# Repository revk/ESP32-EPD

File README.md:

# ESP32-EPD

Now at [Codeberg](https://codeberg.org/RevK/ESP32-EPD)

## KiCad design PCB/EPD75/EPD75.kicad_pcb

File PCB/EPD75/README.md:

# EPD75

These files are for use in [KiCad](https://www.kicad.org).

## Trademark

This is an open source project, but bear in mind you cannot sell boards bearing the Andrews & Arnold Ltd name, the A&A logo, the registered trademark AJK logo, or the GS1 allocated EANs assigned to Andrews & Arnold Ltd.

## Images

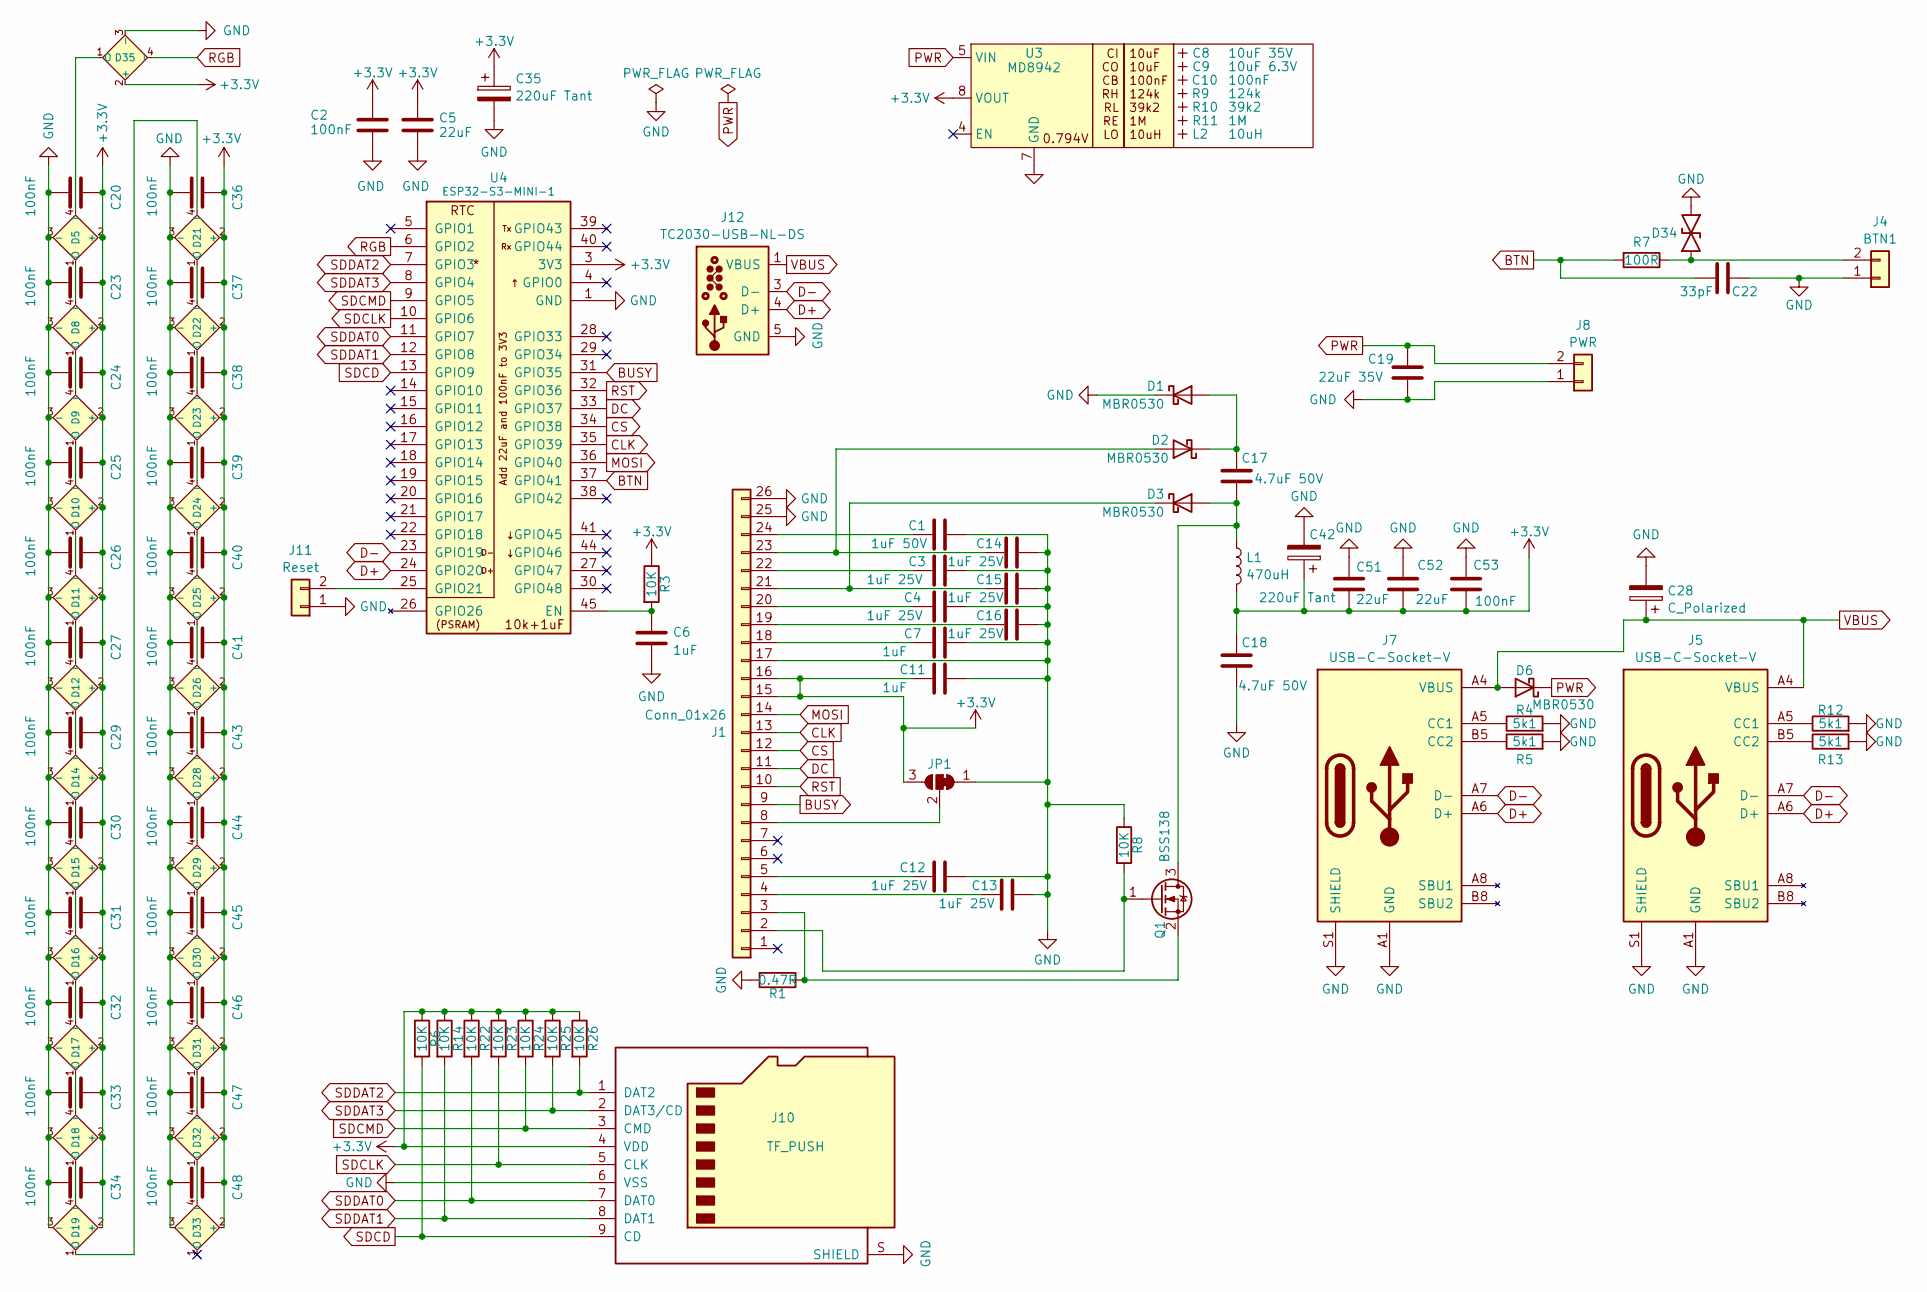
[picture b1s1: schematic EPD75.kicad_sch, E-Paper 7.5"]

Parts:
C1: 1uF 50V; C_0603
C2, C20, C23, C24, C25, C26, C27, C29, C30, C31, C32, C33, C34, C36, C37, C38, C39, C40, C41, C43, C44, C45, C46, C47, C48, C53: 100nF; C_0402
C3, C4, C12, C13, C14, C15, C16: 1uF 25V; C_0402
C5, C51, C52: 22uF; C_0603
C6, C7, C11: 1uF; C_0402
C8: 10uF 35V; C_0603_; MPN C194427
C9: 10uF 6.3V; C_0603_; MPN C1691
C10: 100nF; C_0603_
C17, C18: 4.7uF 50V; C_0805
C19: 22uF 35V; C_1210
C22: 33pF; C_0402
C28: C_Polarized; CP_EIA-7343-31_Kemet-D; MPN C106188
C35, C42: 220uF Tant; CP_EIA-3528-21_Kemet-B; MPN C122649
D1, D2, D3, D6: MBR0530; D_SOD-123; MPN C5204746
D5, D8, D9, D10, D11, D12, D14, D15, D16, D17, D18, D19, D21, D22, D23, D24, D25, D26, D28, D29, D30, D31, D32, D33, D35: XL-1010RGBC-WS2812B; MPN C5349953
D34: DFN1006-2L; MPN C5137770
J1: Conn_01x26; XUNPU-FPC-05FB-24PH20; MPN C2856831
J4: BTN1; WAGO-2060-452-998-404; MPN C2765055
J5, J7: USB-C-Socket-V; USB-C-Socket-H; MPN C709357
J8: PWR; WAGO-2060-452-998-404; MPN C2765055
J10: TF_PUSH; MPN C393941
J11: Reset; AA-Pad
J12: TC2030-USB-NL-DS; Tag-Connect_TC2030-IDC-NL_2x03_P1.27mm_Vertical
JP1: SolderJumper_3_Bridged12; SolderJumper3
L1: 470uH; L_4x4; MPN C42429207
L2: 10uH; L_4x4_; MPN C167879
Q1: BSS138; SOT-23; MPN C2938375
R1: 0.47R; R_0402; MPN C2771738
R3, R6, R8, R14, R22, R23, R24, R25, R26: 10K; R_0402
R4, R5, R12, R13: 5k1; R_0402
R7: 100R; R_0402
R9: 124k; R_0402_; MPN C138062
R10: 39k2; R_0402_
R11: 1M; R_0402_
U3: MD8942; SOT-23-6-MD8942; MPN C2684786
U4: ESP32-S3-MINI-1; MPN C3013941

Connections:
+3.3V: C2.1, C5.1, C11.1, C18.2, C20.1, C23.1, C24.1, C25.1, C26.1, C27.1, C29.1, C30.1, C31.1, C32.1, C33.1, C34.1, C35.1, C36.1, C37.1, C38.1, C39.1, C40.1, C41.1, C42.1, C43.1, C44.1, C45.1, C46.1, C47.1, C48.1, C51.2, C52.2, C53.2, D5.2 (+), D8.2 (+), D9.2 (+), D10.2 (+), D11.2 (+), D12.2 (+), D14.2 (+), D15.2 (+), D16.2 (+), D17.2 (+), D18.2 (+), D19.2 (+), D21.2 (+), D22.2 (+), D23.2 (+), D24.2 (+), D25.2 (+), D26.2 (+), D28.2 (+), D29.2 (+), D30.2 (+), D31.2 (+), D32.2 (+), D33.2 (+), D35.2 (+), J1.15, J1.16, J10.4 (VDD), JP1.3 (B), L1.2, R3.1, R6.1, R14.1, R22.1, R23.1, R24.1, R25.1, R26.1, U3.8 (VOUT), U4.3 (3V3)
BTN: C22.1, R7.2, U4.37 (GPIO41)
BUSY: J1.9, U4.31 (GPIO35)
CLK: J1.13, U4.35 (GPIO39)
CS: J1.12, U4.34 (GPIO38)
D+: J5.A6 (D+), J5.B6 (D+), J7.A6 (D+), J7.B6 (D+), J12.4 (D+), U4.24 (GPIO20)
D-: J5.A7 (D-), J5.B7 (D-), J7.A7 (D-), J7.B7 (D-), J12.2 (NC), J12.3 (D-), J12.6 (NC), U4.23 (GPIO19)
DC: J1.11, U4.33 (GPIO37)
GND: C1.2, C2.2, C3.2, C4.2, C5.2, C6.2, C7.2, C11.2, C12.2, C14.2, C15.2, C18.1, C19.2, C20.2, C22.2, C23.2, C24.2, C25.2, C26.2, C27.2, C28.2, C29.2, C30.2, C31.2, C32.2, C33.2, C34.2, C35.2, C36.2, C37.2, C38.2, C39.2, C40.2, C41.2, C42.2, C43.2, C44.2, C45.2, C46.2, C47.2, C48.2, C51.1, C52.1, C53.1, D1.1 (K), D5.3 (-), D8.3 (-), D9.3 (-), D10.3 (-), D11.3 (-), D12.3 (-), D14.3 (-), D15.3 (-), D16.3 (-), D17.3 (-), D18.3 (-), D19.3 (-), D21.3 (-), D22.3 (-), D23.3 (-), D24.3 (-), D25.3 (-), D26.3 (-), D28.3 (-), D29.3 (-), D30.3 (-), D31.3 (-), D32.3 (-), D33.3 (-), D34.1, D35.3 (-), J1.17, J1.25, J1.26, J4.1, J5.A1 (GND), J5.A12 (GND), J5.B1 (GND), J5.B12 (GND), J5.S1 (SHIELD), J7.A1 (GND), J7.A12 (GND), J7.B1 (GND), J7.B12 (GND), J7.S1 (SHIELD), J8.1, J10.6 (VSS), J10.S (SHIELD), J11.1, J12.5 (GND), JP1.1 (A), R1.2, R4.2, R5.2, R8.1, R12.2, R13.2, U3.2 (GND), U3.7 (GND), U4.1 (GND), U4.2 (GND), U4.42 (GND), U4.43 (GND), U4.46 (GND), U4.47 (GND), U4.48 (GND), U4.49 (GND), U4.50 (GND), U4.51 (GND), U4.52 (GND), U4.53 (GND), U4.54 (GND), U4.55 (GND), U4.56 (GND), U4.57 (GND), U4.58 (GND), U4.59 (GND), U4.60 (GND), U4.61 (GND), U4.62 (GND), U4.63 (GND), U4.64 (GND), U4.65 (GND)
MOSI: J1.14, U4.36 (GPIO40)
unnamed: C17.2, D1.2 (A), D2.1 (K)
unnamed: C14.1, D2.2 (A), J1.23
unnamed: C17.1, D3.2 (A), L1.1, Q1.3 (D)
unnamed: C15.1, D3.1 (K), J1.21
unnamed: D5.1 (O), D8.4 (I)
unnamed: D8.1 (O), D9.4 (I)
unnamed: D9.1 (O), D10.4 (I)
unnamed: D10.1 (O), D11.4 (I)
unnamed: D11.1 (O), D12.4 (I)
unnamed: D12.1 (O), D14.4 (I)
unnamed: D14.1 (O), D15.4 (I)
unnamed: D15.1 (O), D16.4 (I)
unnamed: D16.1 (O), D17.4 (I)
unnamed: D17.1 (O), D18.4 (I)
unnamed: D18.1 (O), D19.4 (I)
unnamed: D19.1 (O), D21.4 (I)
unnamed: D21.1 (O), D22.4 (I)
unnamed: D22.1 (O), D23.4 (I)
unnamed: D23.1 (O), D24.4 (I)
unnamed: D24.1 (O), D25.4 (I)
unnamed: D25.1 (O), D26.4 (I)
unnamed: D26.1 (O), D28.4 (I)
unnamed: D28.1 (O), D29.4 (I)
unnamed: D29.1 (O), D30.4 (I)
unnamed: D30.1 (O), D31.4 (I)
unnamed: D31.1 (O), D32.4 (I)
unnamed: D32.1 (O), D33.4 (I)
unnamed: D5.4 (I), D35.1 (O)
unnamed: J1.2, Q1.1 (G), R8.2
unnamed: J1.3, Q1.2 (S), R1.1
unnamed: C12.1, J1.5
unnamed: J1.8, JP1.2 (C)
unnamed: C7.1, J1.18
unnamed: C4.1, J1.20
unnamed: C1.1, J1.24
unnamed: D34.2, J4.2, R7.1
unnamed: J5.A5 (CC1), R12.1
unnamed: J5.B5 (CC2), R13.1
unnamed: J7.A5 (CC1), R4.1
unnamed: J7.B5 (CC2), R5.1
unnamed: J11.2, U4.25 (GPIO21)
unnamed: C6.1, R3.2, U4.45 (EN)
PWR: C19.1, D6.1 (K), J8.2, U3.5 (VIN)
RGB: D35.4 (I), U4.6 (GPIO2)
RST: J1.10, U4.32 (GPIO36)
SDCD: J10.9 (CD), R6.2, U4.13 (GPIO9)
SDCLK: J10.5 (CLK), R23.2, U4.10 (GPIO6)
SDCMD: J10.3 (CMD), R24.2, U4.9 (GPIO5)
SDDAT0: J10.7 (DAT0), R22.2, U4.11 (GPIO7)
SDDAT1: J10.8 (DAT1), R14.2, U4.12 (GPIO8)
SDDAT2: J10.1 (DAT2), R26.2, U4.7 (GPIO3)
SDDAT3: J10.2 (DAT3/CD), R25.2, U4.8 (GPIO4)
VBUS: C28.1, D6.2 (A), J5.A4 (VBUS), J5.A9 (VBUS), J5.B4 (VBUS), J5.B9 (VBUS), J7.A4 (VBUS), J7.A9 (VBUS), J7.B4 (VBUS), J7.B9 (VBUS), J12.1 (VBUS)

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
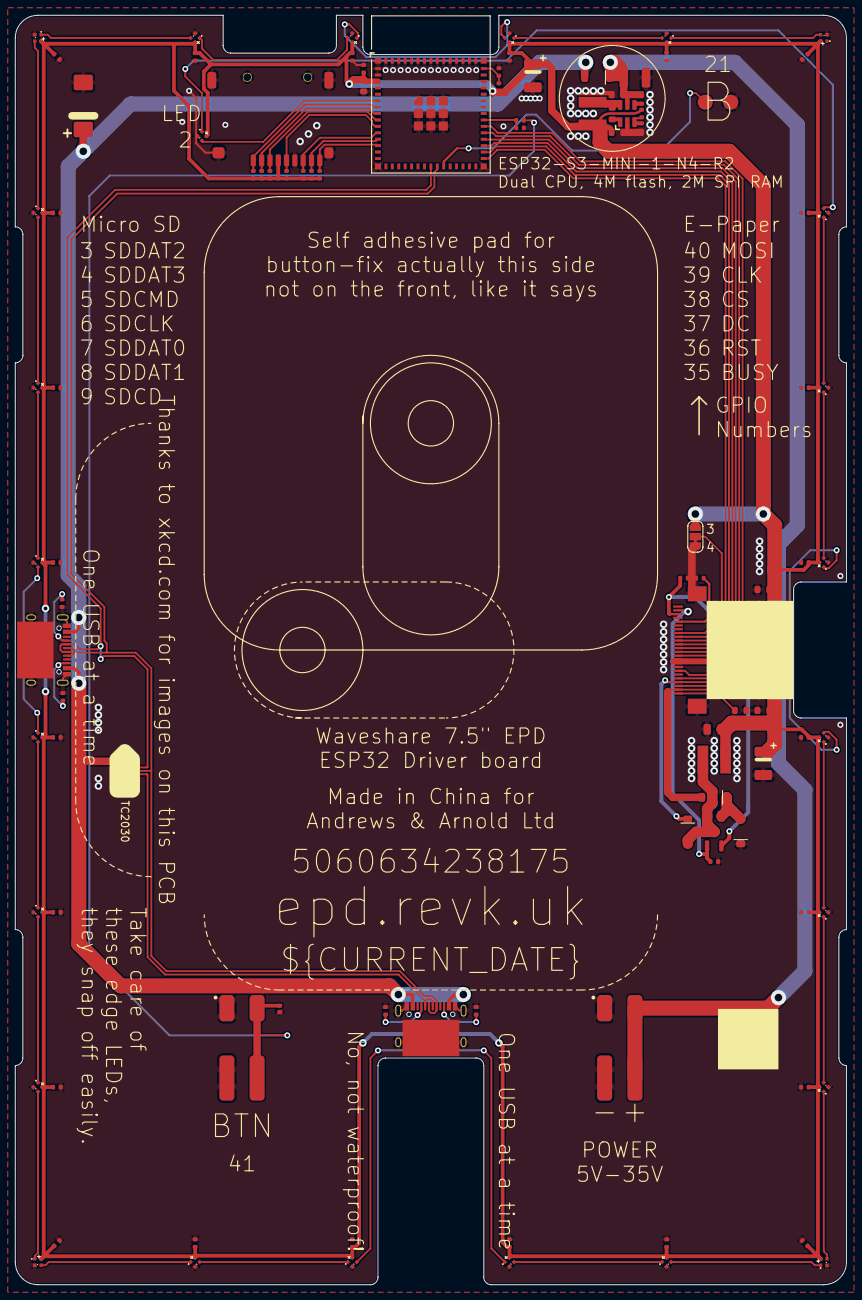
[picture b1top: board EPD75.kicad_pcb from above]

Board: 2 copper layers, 110.0 x 168.0 mm, 110 parts (0 on the bottom side), 64 nets.

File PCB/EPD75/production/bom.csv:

Designator,Footprint,Quantity,Value,LCSC Part #
C1,C_0603,1,1uF 50V,
C10,C_0603_,1,100nF,
"C11, C6, C7",C_0402,3,1uF,
"C12, C14, C15, C3, C4",C_0402,5,1uF 25V,
"C17, C18",C_0805,2,4.7uF 50V,
C19,C_1210,1,22uF 35V,
"C2, C20, C23, C24, C25, C26, C27, C29, C30, C31, C32, C33, C34, C36, C37, C38, C39, C40, C41, C43, C44, C45, C46, C47, C48, C53",C_0402,26,100nF,
C22,C_0402,1,33pF,
C28,CP_EIA-7343-31_Kemet-D,1,C_Polarized,C106188
"C35, C42",CP_EIA-3528-21_Kemet-B,2,220uF Tant,C122649
"C5, C51, C52",C_0603,3,22uF,
C8,C_0603_,1,10uF 35V,C194427
C9,C_0603_,1,10uF 6.3V,C1691
"D1, D2, D3, D6",D_SOD-123,4,MBR0530,C5204746
"D10, D11, D12, D14, D15, D16, D17, D18, D19, D21, D22, D23, D24, D25, D26, D28, D29, D30, D31, D32, D33, D35, D5, D8, D9",SMD1010,25,XL-1010RGBC-WS2812B,C5349953
D34,DFN1006-2L,1,~,C5137770
J1,XUNPU-FPC-05FB-24PH20,1,Conn_01x26,C2856831
J10,TF_PUSH,1,TF_PUSH,C393941
J4,WAGO-2060-452-998-404,1,BTN1,C2765055
"J5, J7",USB-C-Socket-H,2,USB-C-Socket-V,C709357
J8,WAGO-2060-452-998-404,1,PWR,C2765055
L1,L_Ferrocore_DLG-0705,1,470uH,
L2,L_4x4_,1,10uH,
Q1,SOT-23,1,BSS138,C2938375
R1,R_0402,1,0.47R,C2771738
R10,R_0402_,1,39k2,
R11,R_0402_,1,1M,
"R12, R13, R4, R5",R_0402,4,5k1,
"R14, R22, R23, R24, R25, R26, R3, R6, R8",R_0402,9,10K,
R7,R_0402,1,100R,
R9,R_0402_,1,124k,C138062
U3,SOT-23-6-MD8942,1,MD8942,C2684786
U4,ESP32-S3-MINI-1,1,ESP32-S3-MINI-1,C3013941

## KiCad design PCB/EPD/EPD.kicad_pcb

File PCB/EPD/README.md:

# Generic Waveshare e-paper controller board

- ESP32-S3 board (4MiB flash, 2MiB SPIRAM)
- USB-C connector (power and data)
- 4 pin USB header
- 5 pin serial header
- WS2812 RGB LED
- cut/solder pad for 3/4 wire SPI setting (default 4 wire)
- cut/solder pad for 0R47/3R reference (default 0R47)
- pads for two input contacts with BAV99 protection
- pads for power (5V-35V) instead of USB

Works with most waveshare e-paper (not quite all), including large 7.5" panel.

[Amazon UK](https://www.amazon.co.uk/dp/B0CPFM1ZJJ)

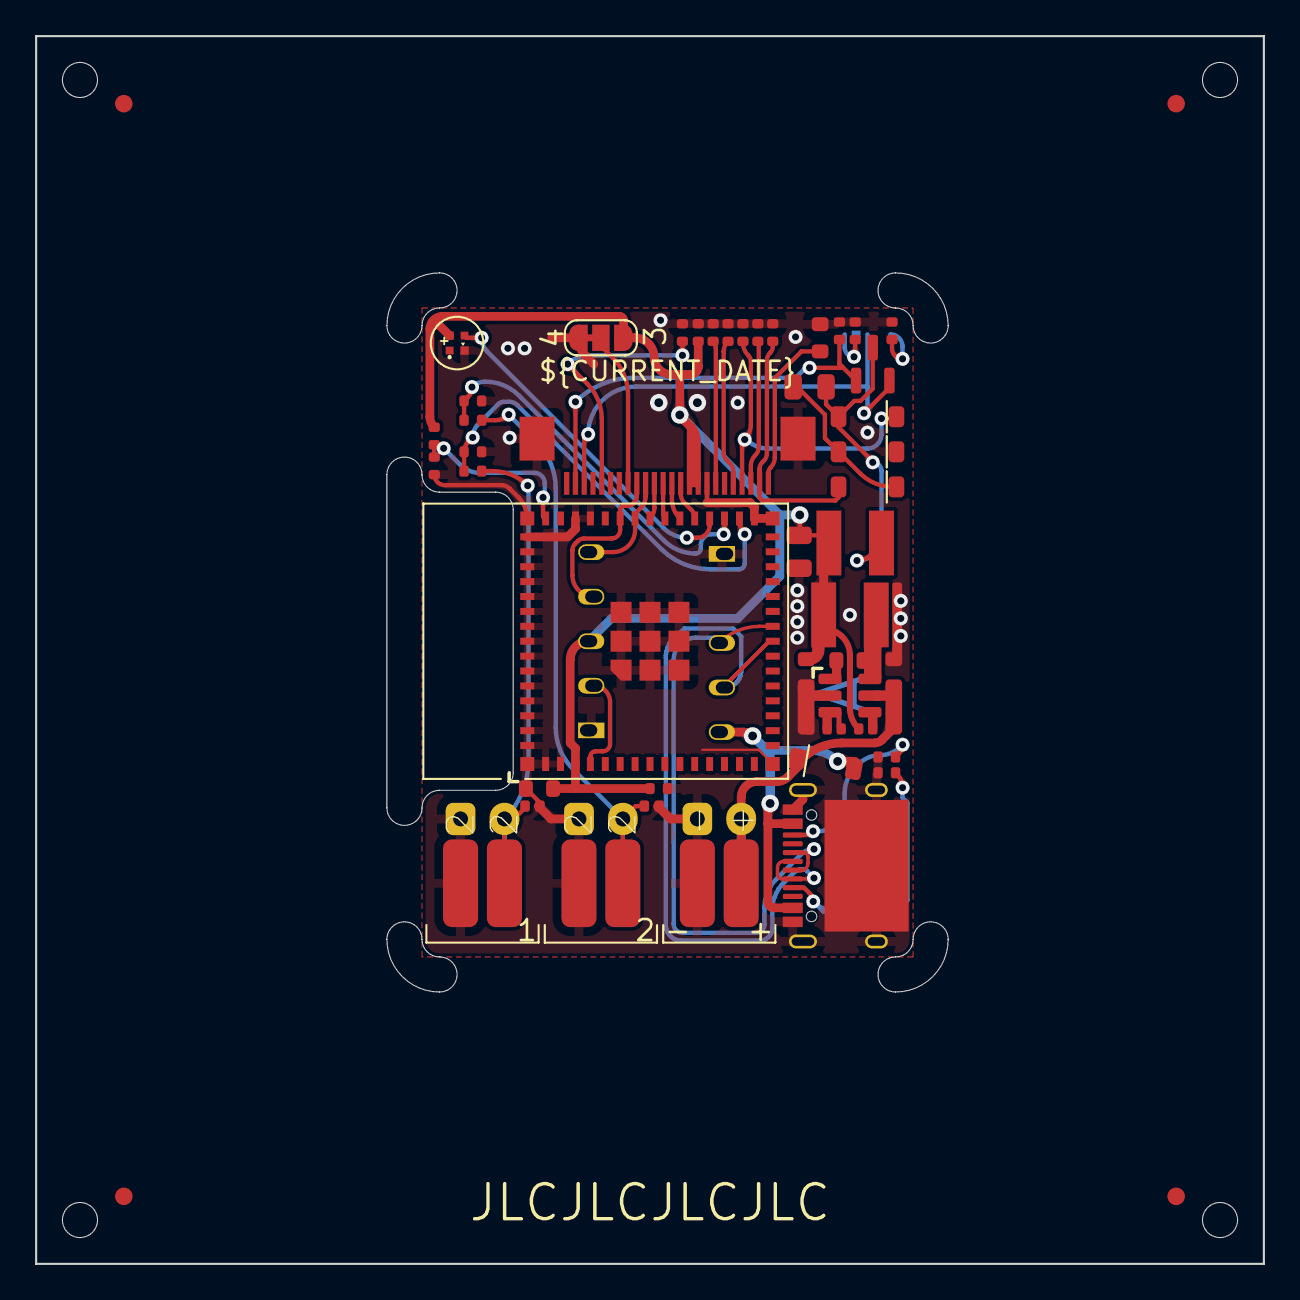
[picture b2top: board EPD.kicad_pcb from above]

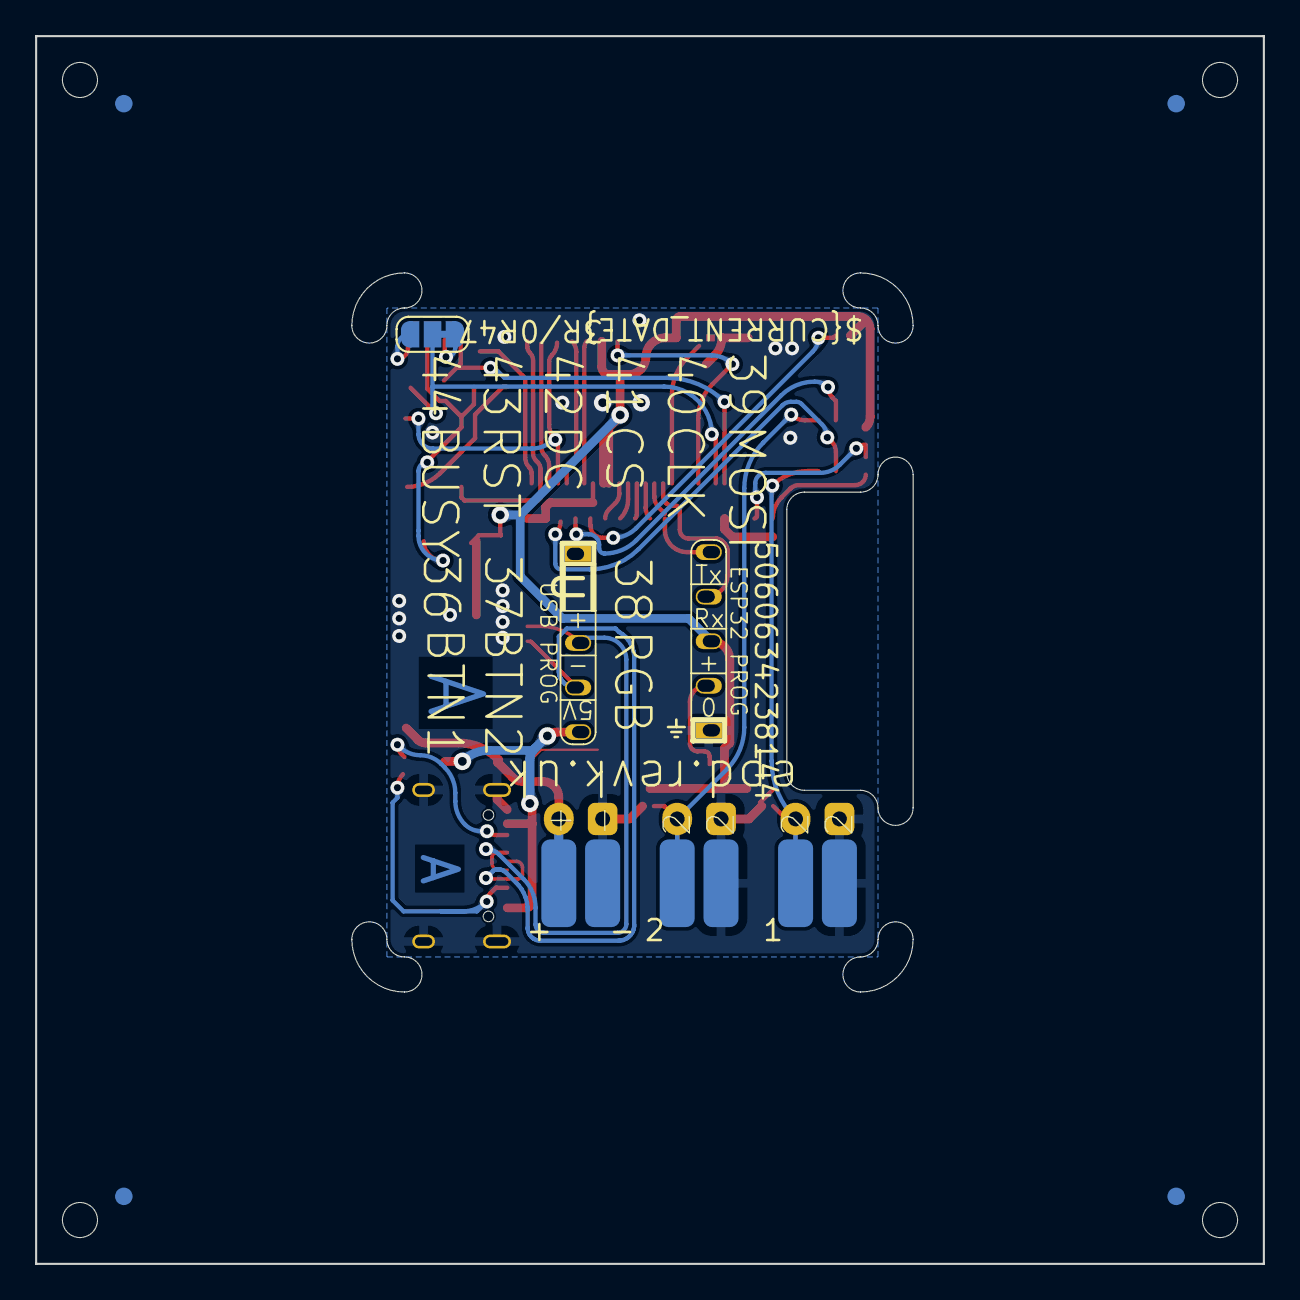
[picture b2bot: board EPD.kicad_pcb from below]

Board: 2 copper layers, 70.0 x 70.0 mm, 67 parts (11 on the bottom side), 35 nets.

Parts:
C1: 1uF 50V; C_0603
C2: 100nF; C_0402
C3, C4, C12, C14, C15: 1uF 25V; C_0402
C5: 22uF; C_0603
C6, C7, C11: 1uF; C_0402
C8: 10uF 35V; C_0603_
C9: 10uF 6.3V; C_0603_
C10: 100nF; C_0603_
C17, C18: 4.7uF 50V; C_0805
C19, C21: 33pF; C_0402
D1, D2, D3, D6: MBR0530; D_SOD-123
D4: XL-1010RGBC-WS2812B; SMD1010
D5, D7: DFN1006-2L
J1: Conn_01x26; XUNPU-FPC-05FB-24PH20
J2: Shelly
J3: USB-PROG
J4, J6: BTN2; PTSM-HH-2-RA
J7: USB-C-Socket-V; USB-C-Socket-H
J8: PWR; PTSM-HH-2-RA
JP1, JP2: SolderJumper_3_Bridged12; SolderJumper3
L1: 470uH; L_4x4
L2: 47uH 1.3A; L_4x4_
P1, P7: +; SolderPadSmall
P2, P8: -; SolderPadSmall
P3, P4, P5, P6, P9, P10, P11, P12: 2; SolderPadSmall
PCB1: 70x70; PCB7070
Q1: BSS138; SOT-23
R1: 0.47R; R_0402
R2: 3R; R_0402
R3, R8: 10K; R_0402
R4, R5: 5k1; R_0402
R6, R7: 100R; R_0402
R9: 124k; R_0402_
R10: 39k2; R_0402_
R11: 1M; R_0402_
U3: MD8942; SOT-23-6-MD8942
U4: ESP32-S3-MINI-1
V1, V3, V4, V6: VCUT70N

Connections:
+3.3V: C2.1, C5.1, C11.1, C18.2, D4.2 (+), J1.15, J1.16, J2.3 (3V3), JP2.3 (B), L1.2, R3.1, U3.8 (VOUT), U4.3 (3V3)
BTN1: C19.1, R7.2, U4.32 (GPIO36)
BTN2: C21.1, R6.2, U4.33 (GPIO37)
BUSY: J1.9, J2.4 (Rx), U4.40 (GPIO44)
CLK: J1.13, U4.36 (GPIO40)
CS: J1.12, U4.37 (GPIO41)
D+: J3.3 (D+), J7.A6 (D+), J7.B6 (D+), U4.24 (GPIO20)
D-: J3.2 (D-), J7.A7 (D-), J7.B7 (D-), U4.23 (GPIO19)
DC: J1.11, U4.38 (GPIO42)
GND: C1.2, C2.2, C3.2, C4.2, C5.2, C6.2, C7.2, C11.2, C12.2, C14.2, C15.2, C18.1, C19.2, C21.2, D1.1 (K), D4.3 (-), D5.1, D7.1, J1.17, J1.25, J1.26, J2.1 (GND), J3.4 (GND), J4.1, J6.1, J7.A1 (GND), J7.A12 (GND), J7.B1 (GND), J7.B12 (GND), J7.S1 (SHIELD), J8.1, JP2.1 (A), P2.1, P4.1, P6.1, P8.1, P10.1, P12.1, R1.2, R2.1, R4.2, R5.2, R8.1, U3.2 (GND), U3.7 (GND), U4.1 (GND), U4.2 (GND), U4.31 (GPIO35), U4.42 (GND), U4.43 (GND), U4.46 (GND), U4.47 (GND), U4.48 (GND), U4.49 (GND), U4.50 (GND), U4.51 (GND), U4.52 (GND), U4.53 (GND), U4.54 (GND), U4.55 (GND), U4.56 (GND), U4.57 (GND), U4.58 (GND), U4.59 (GND), U4.60 (GND), U4.61 (GND), U4.62 (GND), U4.63 (GND), U4.64 (GND), U4.65 (GND)
MOSI: J1.14, U4.35 (GPIO39)
unnamed: C17.2, D1.2 (A), D2.1 (K)
unnamed: C14.1, D2.2 (A), J1.23
unnamed: C17.1, D3.2 (A), L1.1, Q1.3 (D)
unnamed: C15.1, D3.1 (K), J1.21
unnamed: J1.2, Q1.1 (G), R8.2
unnamed: J1.3, JP1.2 (C), Q1.2 (S)
unnamed: C12.1, J1.5
unnamed: J1.8, JP2.2 (C)
unnamed: C7.1, J1.18
unnamed: C4.1, J1.20
unnamed: C3.1, J1.22
unnamed: C1.1, J1.24
unnamed: J2.2 (0), U4.4 (GPIO0)
unnamed: D7.2, J4.2, P5.1, P11.1, R7.1
unnamed: D5.2, J6.2, P3.1, P9.1, R6.1
unnamed: J7.A5 (CC1), R4.1
unnamed: J7.B5 (CC2), R5.1
unnamed: JP1.1 (A), R2.2
unnamed: JP1.3 (B), R1.1
unnamed: C6.1, R3.2, U4.45 (EN)
PWR: D6.1 (K), J8.2, P1.1, P7.1, U3.5 (VIN)
RGB: D4.4 (I), U4.34 (GPIO38)
RST: J1.10, J2.5 (Tx), U4.39 (GPIO43)
VBUS: D6.2 (A), J3.1 (VBUS), J7.A4 (VBUS), J7.A9 (VBUS), J7.B4 (VBUS), J7.B9 (VBUS)

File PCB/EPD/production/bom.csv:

Designator,Footprint,Quantity,Value,LCSC Part #
C1,C_0603,1,1uF 50V,
C10,C_0603_,1,100nF,
"C11, C6, C7",C_0402,3,1uF,
"C12, C14, C15, C3, C4",C_0402,5,1uF 25V,
"C17, C18",C_0402,2,4.7uF,
"C19, C21",C_0402,2,33pF,
C2,C_0402,1,100nF,
C5,C_0603,1,22uF,
C8,C_0603_,1,10uF 35V,C194427
C9,C_0603_,1,10uF 6.3V,C1691
"D1, D2, D3, D6",D_SOD-123,4,MBR0530,C5204746
D4,SMD1010,1,XL-1010RGBC-WS2812B,C5349953
"D5, D7",DFN1006-2L,2,~,C5137770
J1,XUNPU-FPC-05FB-24PH20,1,Conn_01x26,C2856831
J7,USB-C-Socket-H,1,USB-C-Socket-V,C709357
L1,L_4x4,1,10uH,
L2,L_4x4_,1,10uH,
Q1,SOT-23,1,BSS138,C2938375
R1,R_0402,1,0.47R,
R10,R_0402_,1,39k2,
R11,R_0402_,1,1M,
R2,R_0402,1,3R,
"R3, R8",R_0402,2,10K,
"R4, R5",R_0402,2,5k1,
"R6, R7",R_0402,2,100R,
R9,R_0402_,1,124k,
U3,SOT-23-6-MD8942,1,MD8942,C2684786
U4,ESP32-S3-MINI-1,1,ESP32-S3-MINI-1,C3013941

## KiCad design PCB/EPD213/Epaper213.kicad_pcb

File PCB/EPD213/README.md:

# Epaper213

These files are for use in [KiCad](https://www.kicad.org).

## Trademark

This is an open source project, but bear in mind you cannot sell boards bearing the Andrews & Arnold Ltd name, the A&A logo, the registered trademark AJK logo, or the GS1 allocated EANs assigned to Andrews & Arnold Ltd.

## Images

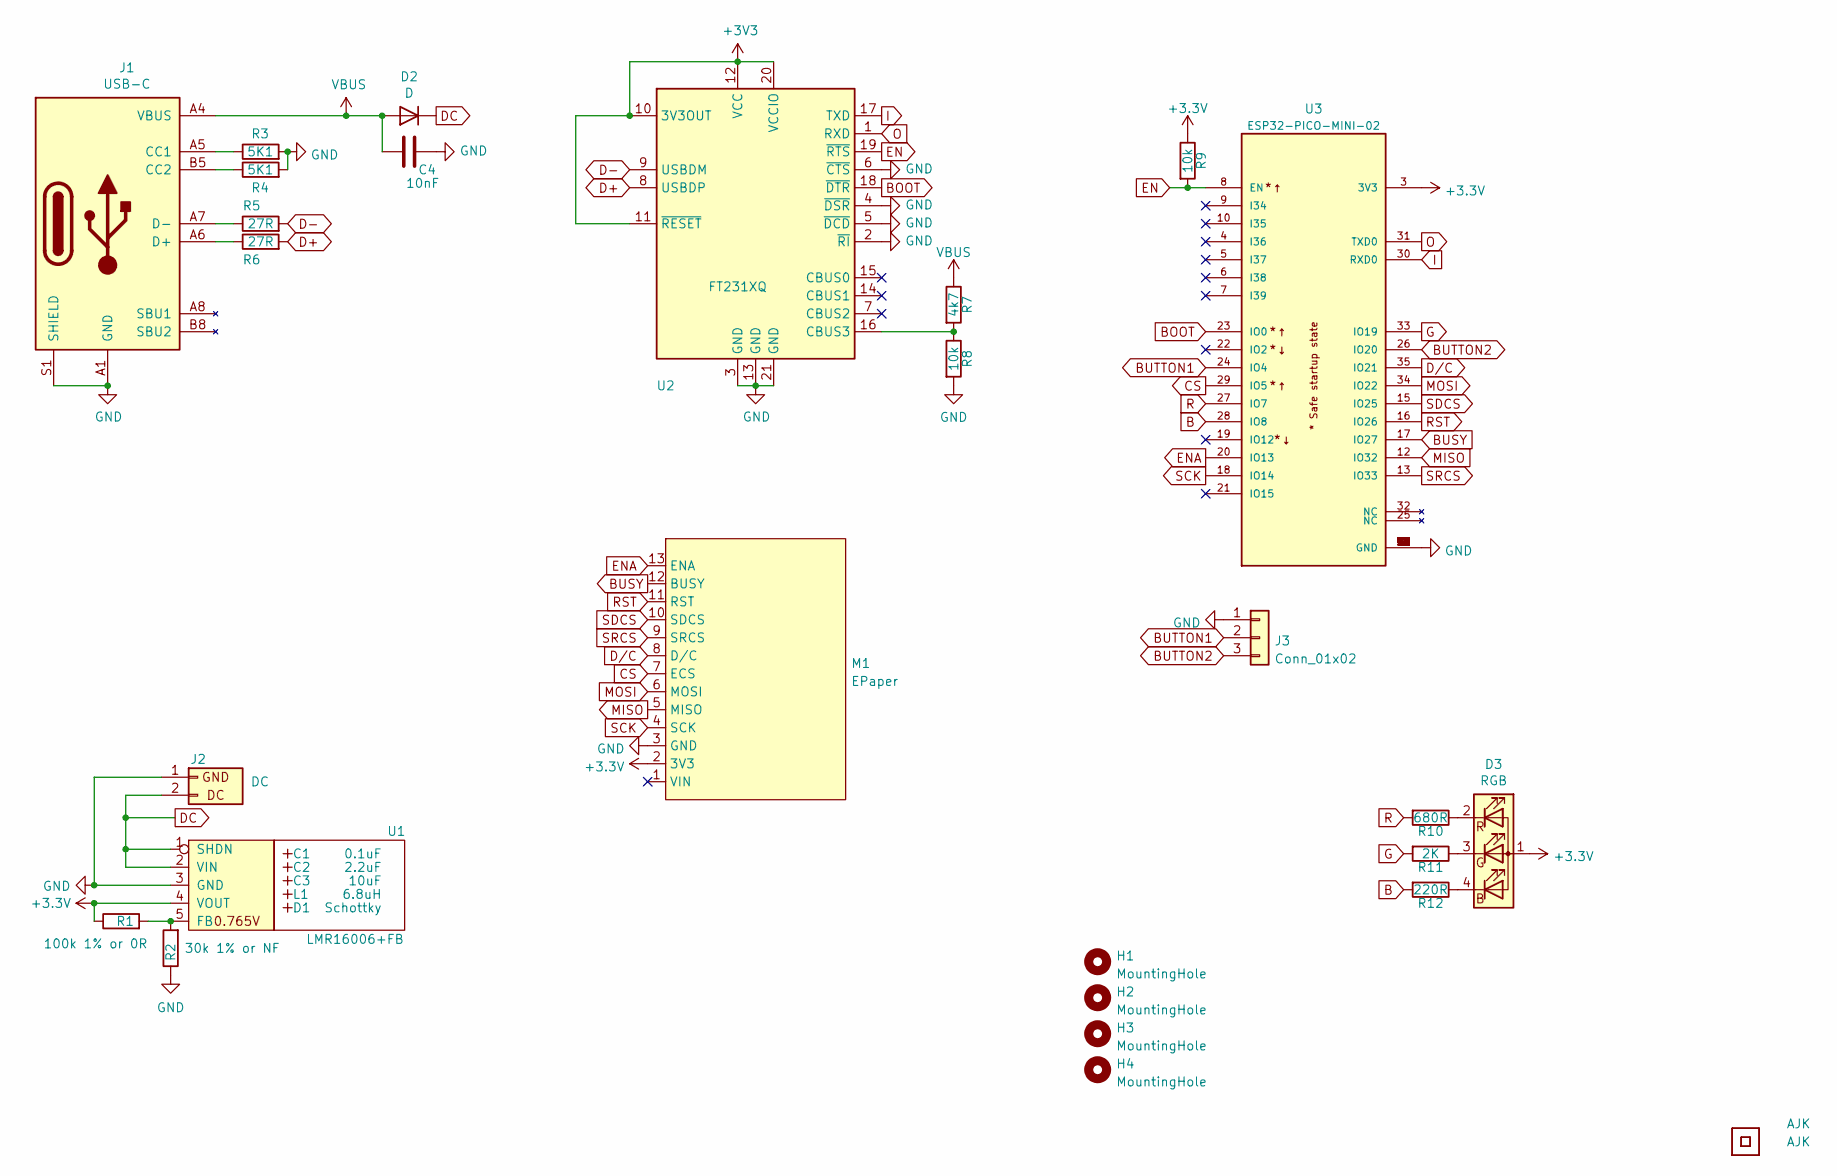
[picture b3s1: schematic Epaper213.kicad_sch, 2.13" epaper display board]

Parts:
C1: 0.1uF; Hidden
C2: 2.2uF; Hidden
C3: 10uF; Hidden
C4: 10nF; C_0603
D1: Schottky; Hidden; Part No CD1206-B2100
D2: D; D_1206
D3: RGB; LED-RGB-1.6x1.6
H1, H2, H3, H4: MountingHole; Hole-2.5mm
J1: USB-C; USC16-TR-Round
J2: DC; Molex_MiniSPOX_H2RA
J3: Conn_01x02; Molex_MiniSPOX_H3RA
L1: 6.8uH; Hidden; Part No TYA4020
Logo1, Logo2: AJK
M1: EPaper; PinHeader_1x13_P2.54mm_Vertical
R1: 100k 1% or 0R; R_0603
R2: 30k 1% or NF; R_0603
R3, R4: 5K1; R_0603
R5, R6: 27R; R_0603
R7: 4k7; R_0603
R8, R9: 10k; R_0603
R10: 680R; R_0603
R11: 2K; R_0603
R12: 220R; R_0603
U1: LMR16006+FB; RegulatorBlockFB; Part No LMR16006YQ3
U2: FT231XQ; QFN-20-1EP_4x4mm_P0.5mm_EP2.5x2.5mm
U3: ESP32-PICO-MINI-02; PARTREV v1.0
U4: QR; QR-GFX

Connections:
B: R12.2, U3.28 (IO8)
BOOT: U2.18 (~DTR), U3.23 (IO0)
BUSY: M1.12 (BUSY), U3.17 (IO27)
BUTTON1: J3.2, U3.24 (IO4)
BUTTON2: J3.3, U3.26 (IO20)
CS: M1.7 (ECS), U3.29 (IO5)
D+: R6.2, U2.8 (USBDP)
D-: R5.2, U2.9 (USBDM)
DC: D2.1 (K), J2.2 (DC), U1.1 (SHDN), U1.2 (VIN)
D/C: M1.8 (D/C), U3.35 (IO21)
EN: R9.2, U2.19 (~RTS), U3.8 (EN)
ENA: M1.13 (ENA), U3.20 (IO13)
G: R11.2, U3.33 (IO19)
GND: C4.1, J1.A1 (GND), J1.A12 (GND), J1.B1 (GND), J1.B12 (GND), J1.S1 (SHIELD), J2.1 (GND), J3.1, M1.3 (GND), R2.1, R3.2, R4.2, R8.2, U1.3 (GND), U2.2 (~RI), U2.3 (GND), U2.4 (~DSR), U2.5 (~DCD), U2.6 (~CTS), U2.13 (GND), U2.21 (GND), U3.1 (GND), U3.2 (GND), U3.11 (GND), U3.14 (GND), U3.36 (GND), U3.37 (GND), U3.38 (GND), U3.39 (GND), U3.40 (GND), U3.41 (GND), U3.42 (GND), U3.43 (GND), U3.44 (GND), U3.45 (GND), U3.46 (GND), U3.47 (GND), U3.48 (GND), U3.49 (GND), U3.50 (GND), U3.51 (GND), U3.52 (GND), U3.53 (GND)
I: U2.17 (TXD), U3.30 (RXD0)
MISO: M1.5 (MISO), U3.12 (IO32)
MOSI: M1.6 (MOSI), U3.34 (IO22)
unnamed: D3.2 (RK), R10.1
unnamed: D3.3 (GK), R11.1
unnamed: D3.4 (BK), R12.1
unnamed: J1.A5 (CC1), R3.1
unnamed: J1.A6 (D+), J1.B6 (D+), R6.1
unnamed: J1.A7 (D-), J1.B7 (D-), R5.1
unnamed: J1.B5 (CC2), R4.1
unnamed: R1.2, R2.2, U1.5 (FB)
unnamed: R7.2, R8.1, U2.16 (CBUS3)
O: U2.1 (RXD), U3.31 (TXD0)
R: R10.2, U3.27 (IO7)
RST: M1.11 (RST), U3.16 (IO26)
SCK: M1.4 (SCK), U3.18 (IO14)
SDCS: M1.10 (SDCS), U3.15 (IO25)
SRCS: M1.9 (SRCS), U3.13 (IO33)
VBUS: C4.2, D2.2 (A), J1.A4 (VBUS), J1.A9 (VBUS), J1.B4 (VBUS), J1.B9 (VBUS), R7.1

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
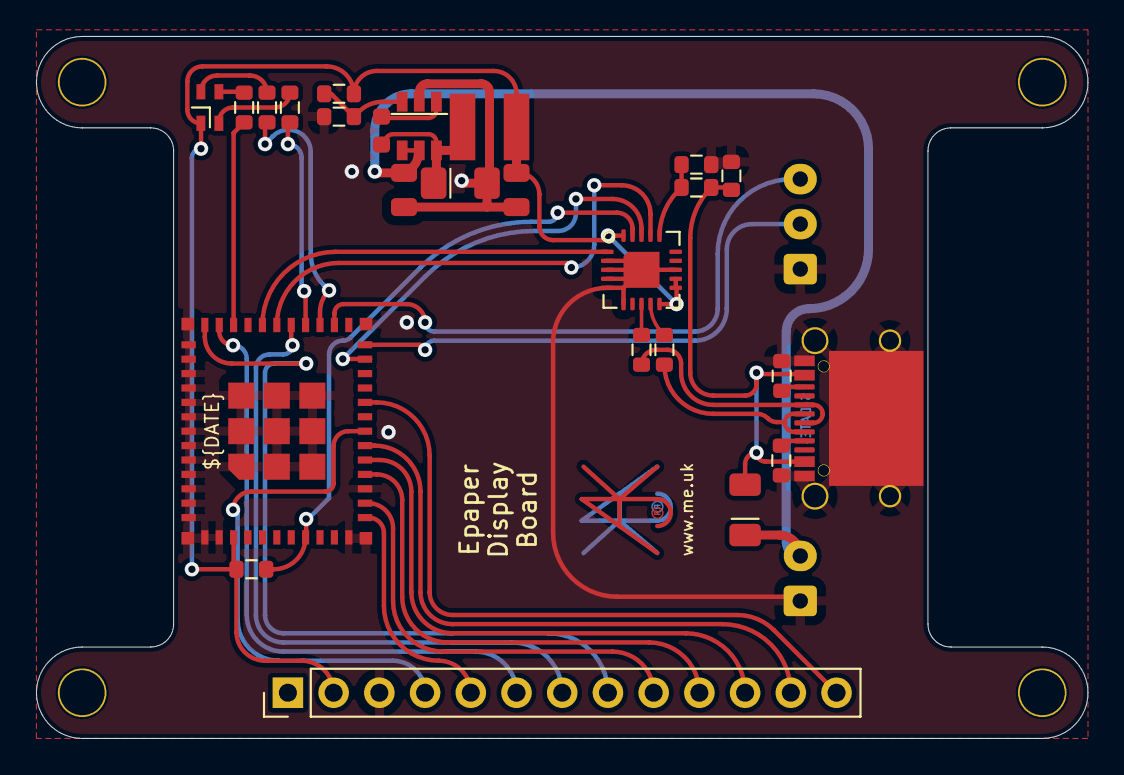
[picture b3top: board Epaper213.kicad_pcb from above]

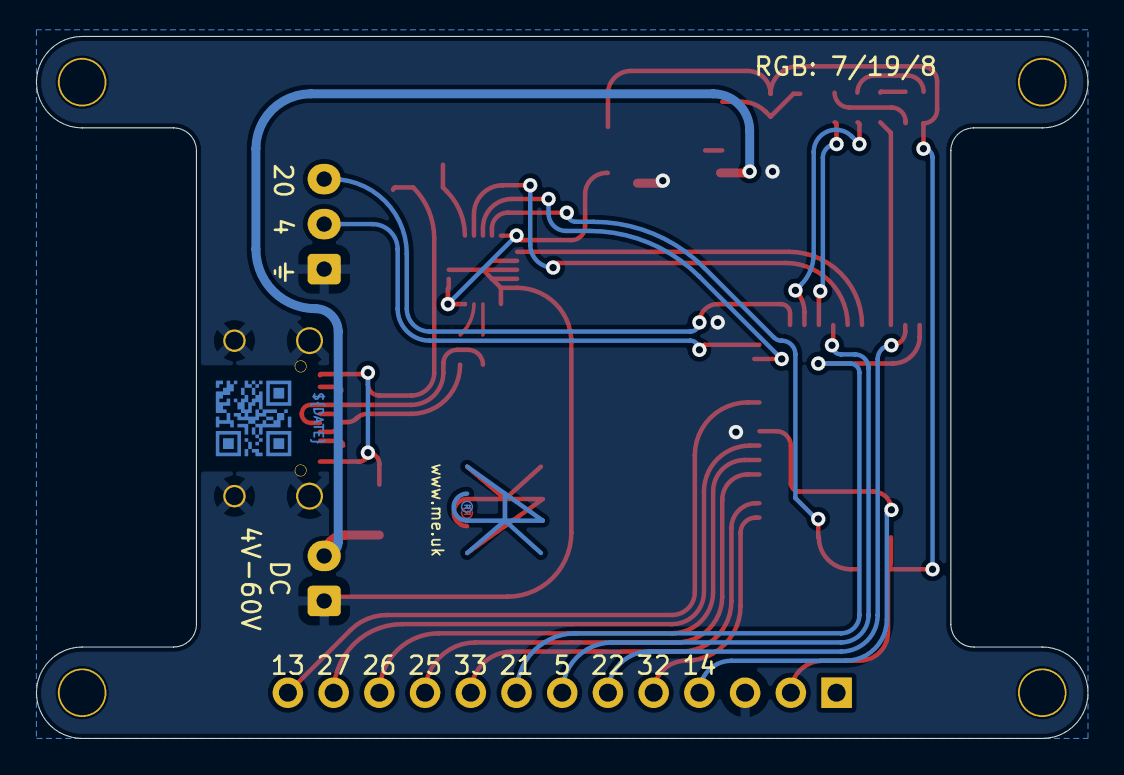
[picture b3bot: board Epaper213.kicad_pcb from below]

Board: 2 copper layers, 58.4 x 39.0 mm, 34 parts (2 on the bottom side), 34 nets.

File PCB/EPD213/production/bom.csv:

Designator,Footprint,Quantity,Value,LCSC Part #
C1,Hidden,1,0.1uF,
C2,Hidden,1,2.2uF,
C3,Hidden,1,10uF,
C4,C_0603,1,10nF,
D1,Hidden,1,Schottky,
D2,D_1206,1,D,
D3,LED-RGB-1.6x1.6,1,RGB,
J1,USC16-TR-Round,1,USB-C,
J2,Molex_MiniSPOX_H2RA,1,DC,
J3,Molex_MiniSPOX_H3RA,1,Conn_01x02,
L1,Hidden,1,6.8uH,
M1,PinHeader_1x13_P2.54mm_Vertical,1,EPaper,
R1,R_0603,1,100k 1% or 0R,
R10,R_0603,1,680R,
R11,R_0603,1,2K,
R12,R_0603,1,220R,
R2,R_0603,1,30k 1% or NF,
"R3, R4",R_0603,2,5K1,
"R5, R6",R_0603,2,27R,
R7,R_0603,1,4k7,
"R8, R9",R_0603,2,10k,
U1,RegulatorBlockFB,1,LMR16006+FB,
U2,QFN-20-1EP_4x4mm_P0.5mm_EP2.5x2.5mm,1,FT231XQ,
U3,ESP32-PICO-MINI-02,1,ESP32-PICO-MINI-02,

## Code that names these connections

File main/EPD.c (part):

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}

void
showlights (const char *rgb)
{
   if (!strip)
      return;
   const char *c = rgb;
   for (int i = 0; i < lightcount; i++)
   {
      uint8_t mode = 0;
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}

void
setlights (const char *rgb)
{
   if (rgb)
   {
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void
sd_task (void *x)
{
   revk_gpio_input (sdcd);
   sdmmc_slot_config_t slot = SDMMC_SLOT_CONFIG_DEFAULT ();
   slot.clk = sdclk.num;
   slot.cmd = sdcmd.num;
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   };
   while (!b.die)
   {
      while (!b.die && !revk_gpio_get (sdcd))
         sleep (1);
      if (b.die)
         break;
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      {
         esp_vfs_fat_info (sd_mount, &sdsize, &sdfree);
         ESP_LOGE (TAG, "SD Mounted %llu/%llu", sdfree, sdsize);
         while (!b.die && revk_gpio_get (sdcd))
            sleep (1);
         esp_vfs_fat_sdcard_unmount (sd_mount, card);
         card = NULL;
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      uint32_t b = revk_blinker ();
      for (int i = 0; i < sizeof (lightmode) / sizeof (*lightmode); i++)
         if (lightmode[i] == REVK_SETTINGS_LIGHTMODE_SD_STATUS)
            revk_led (strip, i, 255, revk_rgb (card ? 'G' : revk_gpio_get (sdcd) ? 'R' : 'Y'));
         else if (lightmode[i] == REVK_SETTINGS_LIGHTMODE_STATUS)
            revk_led (strip, i, 255, b);
      led_strip_refresh (strip);
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   if (nfctx.set && nfcrx.set)
      revk_task ("nfc", nfc_task, NULL, 8);
   {                            // GFX
    const char *e = gfx_init (pwr: gfxpwr.num, ena: gfxena.num, cs: gfxcs.num, sck: gfxsck.num, mosi: gfxmosi.num, dc: gfxdc.num, rst: gfxrst.num, busy: gfxbusy.num, flip: gfxflip, direct: 1, invert:gfxinvert);
      if (e)
      {
         ESP_LOGE (TAG, "gfx %s", e);
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
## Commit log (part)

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2025-04-16 Library update
2025-04-16 Beta
2025-04-16 Release
2025-04-16 clock tweak
2025-04-17 number formatting
2025-04-18 Tweak text size
2025-04-18 Image invert
2025-04-18 Lights based on sunset and sunrise
2025-04-19 Blocky and dotty
2025-04-19 Clock changes and font changes
2025-04-19 Timezone overrides
2025-04-21 faster weather get at start
2025-04-21 Tidy
2025-04-21 Misisng weather data some time, fixed
2025-04-21 Bins crash
2025-04-21 Cache issue
2025-04-22 Tweak wordiing
2025-04-23 Better default for small displays
2025-04-23 VEML6040
2025-04-23 MCP9808
2025-04-24 Pressure
2025-04-24 T6793 CO2
2025-04-24 CO2 fixed
2025-04-24 SCD41
2025-04-24 hPa 2 places
2025-04-25 Various tweaks and correct pressure
2025-05-01 TMP1075
2025-05-01 Error cHeck
2025-05-01 Offset
2025-05-03 No temp
2025-05-04 Clean up sensors
2025-05-06 ds ha announce
2025-05-07 First attempt at scd41to
2025-05-08 Many tweaks including SCD41 temp offset
2025-05-08 /status
2025-05-08 ensor info
2025-05-08 Sensors
2025-05-08 More DS18B20 on HA, and a blind build
2025-05-08 Blind build
2025-05-13 Started on BLE
2025-05-13 BLE MAC match
2025-05-15 SCD41 startup
2025-05-15 VEML retry
2025-05-16 HA now has BLE RH and Bat and named BLE.
2025-05-16 Fix TMP1075 offset (was backwards!)
2025-05-16 PWM backlight
2025-05-16 Temperature colour override
2025-05-16 low/high display levels
2025-05-17 memory usage
2025-05-18 Started buttons
2025-05-18 btn twaek
2025-05-18 More work on buttons
2025-05-18 btnp
2025-05-18 short/long press logic
2025-05-18 Buttons in to HA now
2025-05-18 Buttons
2025-05-22 Added latest release binaries
2025-05-22 Better reboot screen
2025-05-22 Nicer reboot sceren
2025-05-27 Testign
2025-05-27 message command
2025-05-27 Invalid DS18B20 temp
2025-05-28 New $API and apiurl
2025-05-28 API tested
2025-05-28 New number formatting
2025-05-28 SHT40 settings
2025-05-28 IR GPIO
2025-05-28 Settings for new bits
2025-05-28 SHT40 handling
2025-05-28 I2S settings added
2025-05-29 chache
2025-05-29 Cache rework
2025-05-29 Testing
2025-05-29 Noise
2025-05-29 Tinker
2025-05-29 SCD41v offset correctionm
2025-05-29 LED controls
2025-05-29 Some IR logging
2025-05-29 Cleaner IR
2025-05-30 IR keys and HA
2025-05-30 SHT40
2025-05-30 Tidy for Daikin timing
2025-05-30 db tidy
2025-05-31 Tidy IR
2025-06-02 Special IR
2025-06-03 Cleaner fade
2025-06-06 Logs
2025-06-30 New countdown formatting
2025-06-30 Debug
2025-06-30 month
2025-07-05 FFS -inf
2025-07-06 temperaure unit
2025-07-06 Nested $ expansion
2025-09-28 New LEDs
2025-09-28 Regulator update
2025-09-28 SS fixes
2025-09-29 DESFire library
2025-09-29 Added PN532 library
2025-09-29 Fob report on MQTT
2025-09-29 Tidy logging
2025-11-01 Updated NFC, and re-render
2025-11-01 ADded DS18B20
2025-11-06 Ready for order
2025-11-09 latest lib
2025-11-10 Add ATQ/SAK
2025-11-10 type
2025-11-10 handle cards
2025-11-10 NTAG
2025-11-11 Working on NTAG still
2025-11-11 FFS, OK works for URL but not for WiFi
2025-11-12 More NTAG tweaks
2025-11-15 New OTA
2025-11-18 New panel type
2025-11-18 Manifest
2025-11-18 Settings ATE
2025-11-18 Console
2025-11-18 ATE fails
2025-11-18 ATE comment
2025-11-18 ATE wait
2025-11-18 tweak
2025-11-28 D'Oh
2025-12-09 Stupid
2025-12-09 Backwards "next collection" on council website

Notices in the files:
main/EPD.c:
Copyright ©2019 - 2025 Adrian Kennard, Andrews & Arnold Ltd.See LICENCE file for details .GPL 3.0
